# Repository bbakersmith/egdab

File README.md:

# Egdab

An orchid shaped conference badge built around an ATTiny1606, created for
DefCon 27. Features audio, temperature, and touch sensors, as well as numerous
buttons, dipswitches, and potentiometers for user input. Outputs in the form of
several RGB LEDs and a two digit seven segment display.

\
Front

\
Back

# License

Copyright Ben Baker-Smith 2019.

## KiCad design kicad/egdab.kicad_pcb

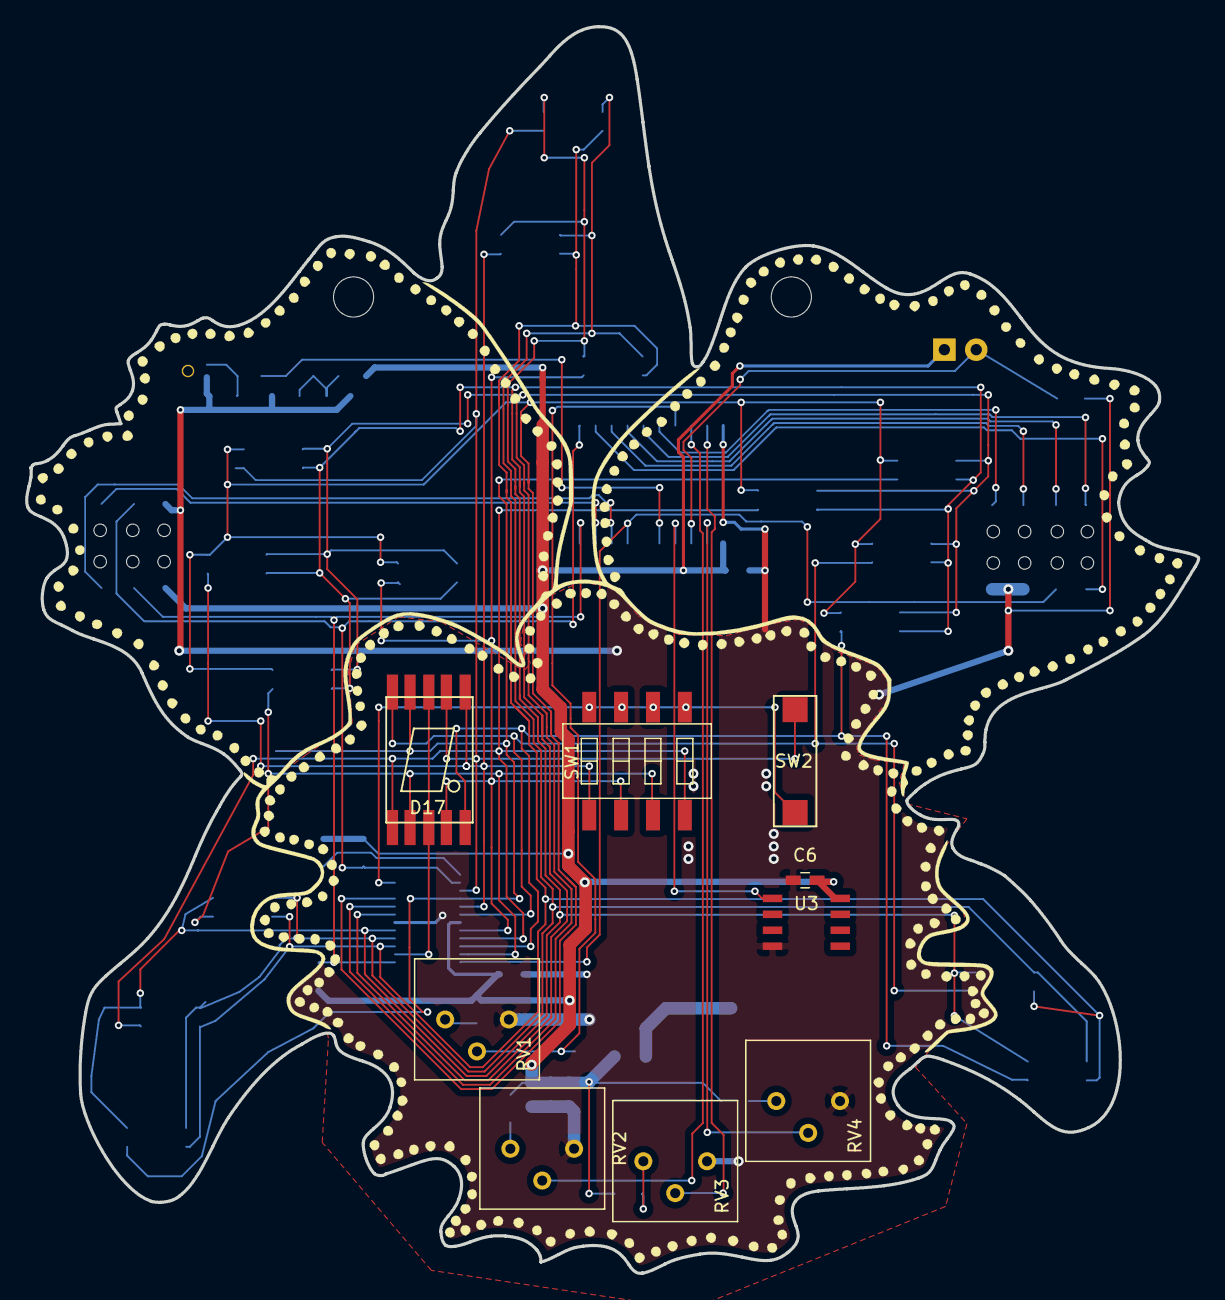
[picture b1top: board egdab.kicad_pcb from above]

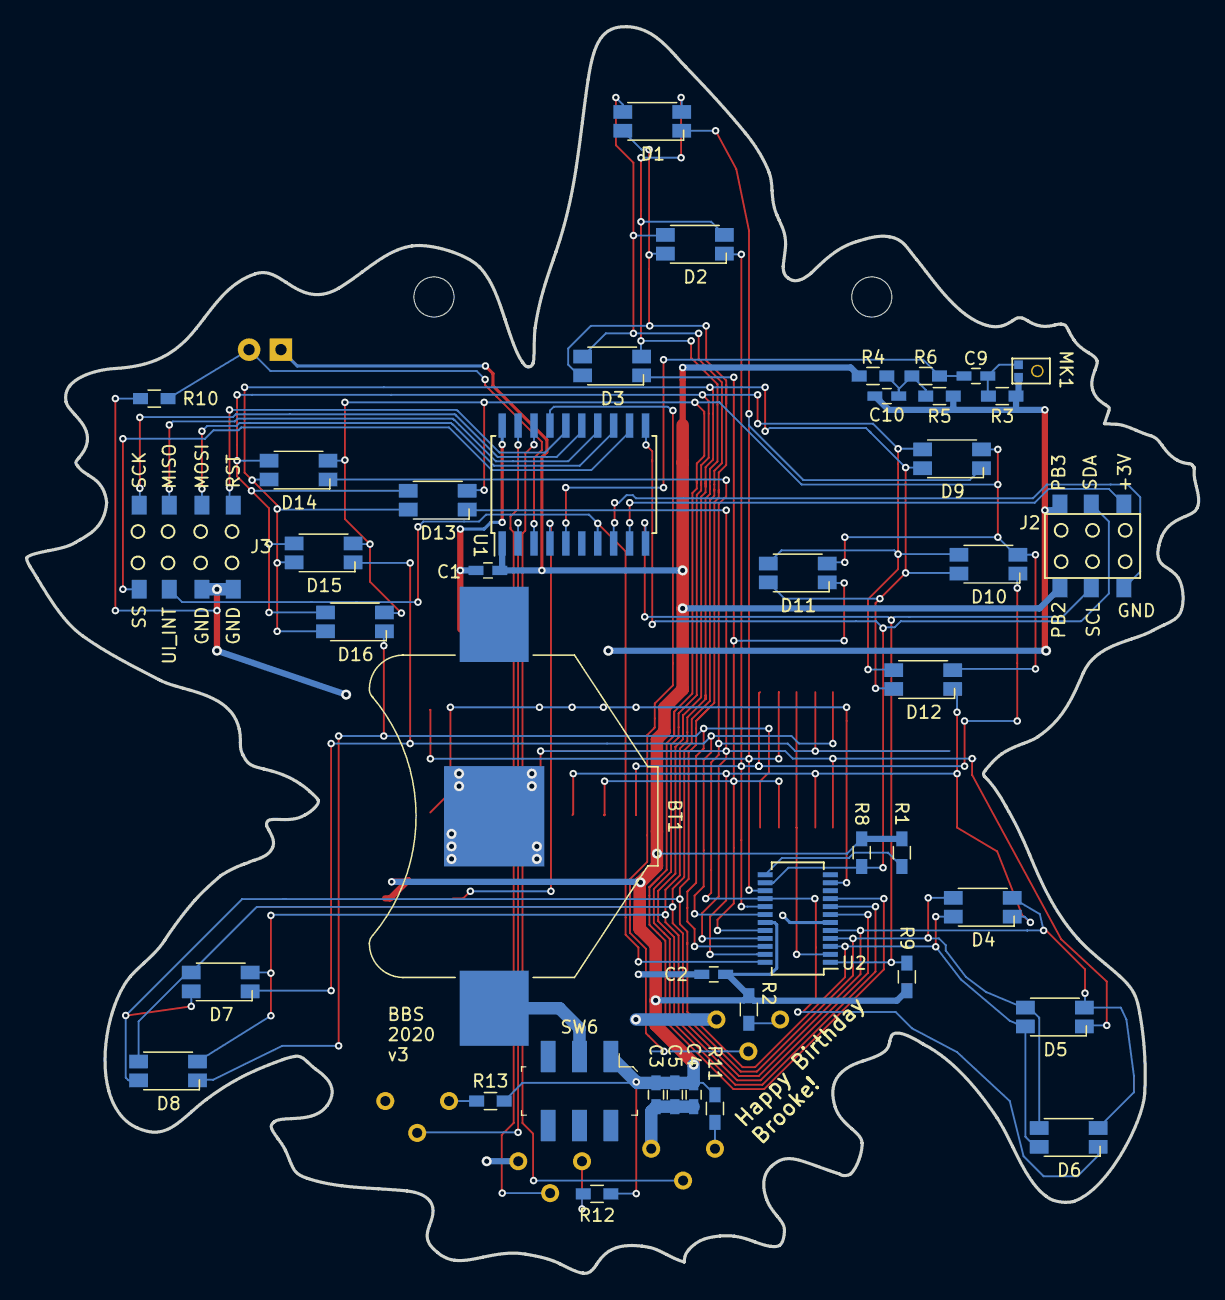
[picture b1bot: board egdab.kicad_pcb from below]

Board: 4 copper layers, 93.4 x 99.4 mm, 52 parts (42 on the bottom side), 43 nets.

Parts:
BT1: CR2450VP; Keystone_3008_1x2450-CoinCell
C1, C2, C3, C4, C5, C6: 22uF; C_0603_HandSoldering
C9, C10: 10uF; C_0603_HandSoldering
D1, D2, D3, D4, D5, D6, D7, D8, D9, D10, D11, D12, D13, D14, D15, D16: LED_RGB; LED_RGB_SMD_PLCC4_Reverse_XZMDKCBDDG45S
D17: 7SegmentLED_ACSC02
J2: Conn_02x03_Counter_Clockwise; Header_SMD_vertical_passthrough_02x03
J3: Conn_02x04_Counter_Clockwise; Header_SMD_vertical_passthrough_02x04
MK1: Microphone; spv1840l45h-b
R1: 22K; R_0603_HandSoldering
R2, R3, R4, R5, R6, R10, R11, R12, R13: 10K; R_0603_HandSoldering
R7: R_PHOTO; LED_D4.0mm
R8, R9: 4K7; R_0603_HandSoldering
RV1, RV2, RV3, RV4: R_POT; Potentiometer_Trimmer_Suntan_TSR-3386P_Horizontal
SW1: SW_DIP_x04; SW_DIP_x4_W8.61mm_Slide_LowProfile
SW2: SW_Push; SW_SPST_SMD_3_6
SW6: SW_SPST; Switch_Slide_JS202011SCQN
U1: ATtiny1606-S; SOIC-20W_7.5x12.8mm_Pitch1.27mm
U2: AS1115-BSST; SSOP-24_3.9x8.7mm_Pitch0.635mm
U3: LM35-D; SOIC-8_3.9x4.9mm_Pitch1.27mm

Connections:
+3V0: C1.1, C2.1, C3.1, C4.1, C5.1, C6.1, J2.6, R1.1, R2.2, R4.1, R7.1, R8.2, R9.2, R11.2, R12.2, R13.2, SW6.1, U1.1, U2.19, U3.8
/AS1115_ISET: R1.2, U2.13
/AUDIO: C9.2, R6.1, U1.5
/BAT+: BT1.1, SW6.2
/DIG0: D17.3, D17.8, U2.2
/DIG1: D1.1, D2.1, D3.1, D4.1, D5.1, D6.1, D7.1, D8.1, U2.3
/DIG2: D1.4, D2.4, D3.4, D4.4, D5.4, D6.4, D7.4, D8.4, U2.4
/DIG3: D1.3, D2.3, D3.3, D4.3, D5.3, D6.3, D7.3, D8.3, U2.5
/DIG4: D9.1, D10.1, D11.1, D12.1, D13.1, D14.1, D15.1, D16.1, U2.7
/DIG5: D9.4, D10.4, D11.4, D12.4, D13.4, D14.4, D15.4, D16.4, U2.8
/DIG6: D9.3, D10.3, D11.3, D12.3, D13.3, D14.3, D15.3, D16.3, U2.9
/KEYA: SW1.5, SW1.6, SW1.7, SW1.8, SW2.2, U2.11
/PHOTO: R7.2, R10.1, U1.3
/P_CHROMA+: RV3.2, U1.19
/P_CHROMA-: RV2.2, U1.18
/P_LUMA: RV1.2, U1.17
/P_TIME: RV4.2, U1.2
/SEGA: D1.2, D9.2, D17.7, SW2.1, U2.15
/SEGB: D2.2, D10.2, D17.6, SW1.1, U2.17
/SEGC: D3.2, D11.2, D17.4, SW1.2, U2.20
/SEGD: D4.2, D12.2, D17.2, SW1.3, U2.23
/SEGDP: D8.2, D16.2, D17.5, U2.22
/SEGE: D5.2, D13.2, D17.1, SW1.4, U2.21
/SEGF: D6.2, D14.2, D17.9, U2.16
/SEGG: D7.2, D15.2, D17.10, U2.18
/TEMP: U1.4, U3.1
GND: BT1.2, C1.2, C2.2, C3.2, C4.2, C5.2, C6.2, C10.1, J2.1, J3.1, J3.2, MK1.1, R3.2, R5.2, R10.2, RV1.3, RV2.3, RV3.3, RV4.3, U1.20, U2.6, U3.4
I2C_SCL: J2.2, R8.1, U1.11, U2.14
I2C_SDA: J2.5, R9.1, U1.10, U2.1
unnamed: C9.1, MK1.2, R3.1
unnamed: C10.2, R4.2, R5.1, R6.2
unnamed: R2.1, RV1.1
unnamed: R11.1, RV2.1
unnamed: R12.1, RV3.1
unnamed: R13.1, RV4.1
PB2: J2.3, U1.9
PB3: J2.4, U1.8
RESET: J3.8, U1.16
SPI_MISO: J3.6, U1.14
SPI_MOSI: J3.7, U1.13
SPI_SCK: J3.5, U1.15
SPI_SS: J3.4, U1.12
UI_INTERRUPT: J3.3, U1.7, U2.24

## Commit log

2019-06-16 Init
2019-06-17 Schematic WIP
2019-06-18 Global labels
2019-06-18 AS1115 takeover, needs diodes for keyscan
2019-06-18 ATtiny1606 instead of Atmega328p
2019-06-20 First draft of schematic
2019-06-21 PCB WIP
2019-06-28 Big things
2019-06-30 PCB layout progress
2019-07-03 Draft 1 may be complete
2019-07-04 Moar
2019-07-04 v2 PCB in progress
    - board version added to silk
    - use actual reverse mount RGB LEDs
    - invert lower petal soldermask
2019-07-23 First attempt to write source code
2019-07-31 Atmel studio bullshit start
2019-07-31 Well, TWI is sorta kinda working maybe
2019-07-31 Linux programming!
2019-08-06 Linux programming! ByoArray queue TWI write kinda working with queue Include necessary atpack headers
2019-08-06 Queue docs
2019-08-15 Color
2019-08-15 Color to digits, no intensity
2019-08-15 Hue to digits
2019-08-16 Controller apply range
2019-08-16 Oscillator
2019-08-16 Map analog inputs to LED hue and value
2019-08-17 Preparing to switch to twi module
2019-08-19 Move LED structs and fns into controller
2019-08-19 controller_update_ui_output to controller_update_led_output
2019-08-20 LED color control IRL
2019-08-21 Rotating colors working IRL
2019-09-17 WIP to integrate TWI lib
2019-10-21 README
2020-02-06 PCB v2 redesign WIP
2020-02-11 V3 ordered
2020-08-19 new board RGB LED controll and 7-seg digits
